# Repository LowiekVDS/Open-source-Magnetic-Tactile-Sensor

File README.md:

### TL;DR

[Paper](https://arxiv.org/abs/2405.18582), also see [this repo](https://github.com/LowiekVDS/masters-thesis) for expanded design.

# Open-source Magnetic Tactile Sensing

This repo contains the design files for a magnetic tactile fingertip presented at the [ViTac workshop](https://shanluo.github.io/ViTacWorkshops/) at ICRA2024, you can read the paper [here](https://arxiv.org/abs/2405.18582).
The fingertip has four taxels in a 2-by-2 grid. We developed a calibration method to be used with a robotic arm with integrated F/T sensor. In the paper, the fingertip is mounted to (a gripper the arm and pushed against an external probe to collect calibration data. It is crucial that the mounting of the fingertip to the robot is rigid. We have noticed that this is not sufficiently the case when mounting the fingertip to a Robotiq 2F-85 gripper. A Schunk EGK-40 gave better results. 

This work was expanded upon by designing a 4-by-8 grid as well, together with a more reliable calibration method where the sensor is mounted to the table, see [this repo](https://github.com/LowiekVDS/masters-thesis).

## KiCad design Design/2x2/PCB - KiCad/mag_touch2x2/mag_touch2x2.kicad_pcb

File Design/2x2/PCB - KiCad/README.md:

The KiCad component schematics and footprints are in the `lib` folder, make sure to add them in KiCad (Preferences > Manage Symbol Libraries && Preferences > Manage Footprint Libraries).

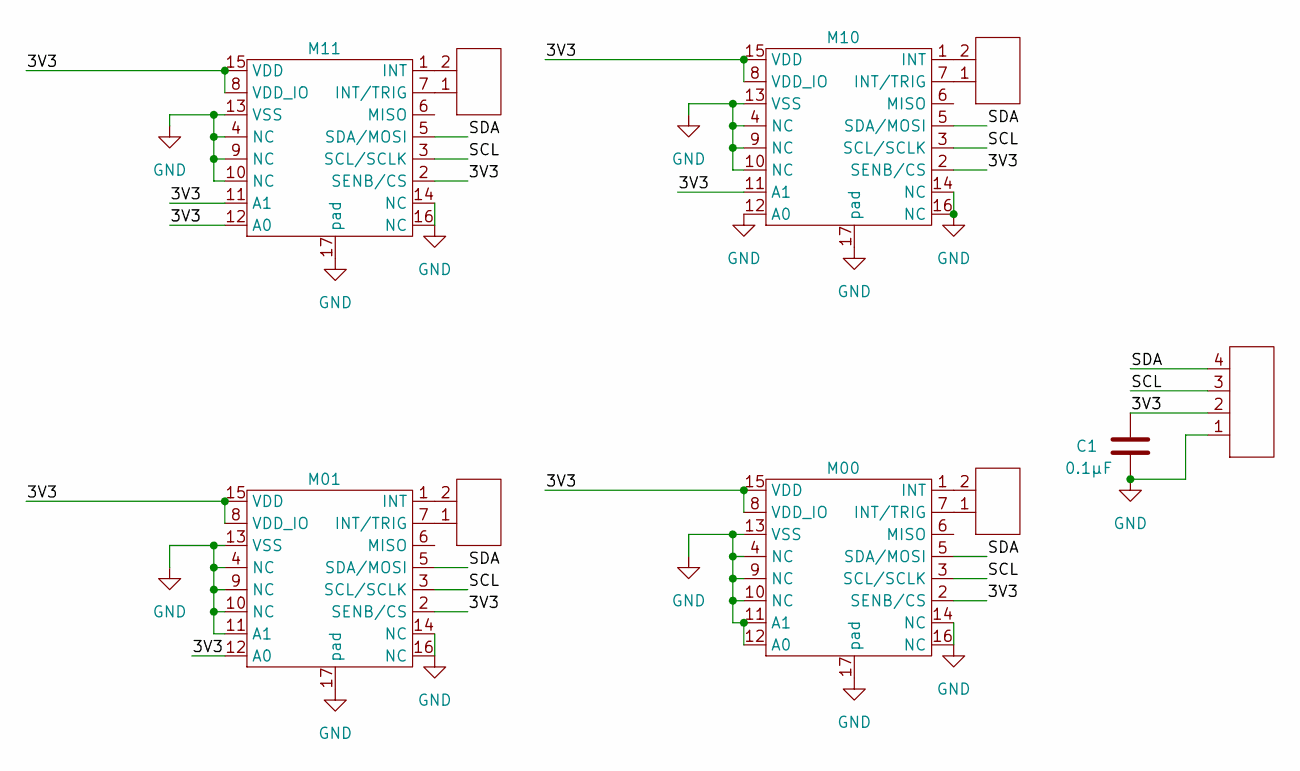
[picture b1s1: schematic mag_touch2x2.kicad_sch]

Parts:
C1: 0.1µF; C_0603_1608Metric
I1: 2POS_INTERFACE; 4POS_INTERFACE
I2, I3, I4, I5: 2POS_INTERFACE
M00, M01, M10, M11: QFN50P300X300X100-17N

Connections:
/3V3: C1.1, I1.2, M00.2 (SENB/CS), M00.8 (VDD_IO), M00.15 (VDD), M01.2 (SENB/CS), M01.8 (VDD_IO), M01.12 (A0), M01.15 (VDD), M10.2 (SENB/CS), M10.8 (VDD_IO), M10.11 (A1), M10.15 (VDD), M11.2 (SENB/CS), M11.8 (VDD_IO), M11.11 (A1), M11.12 (A0), M11.15 (VDD)
/SCL: I1.3, M00.3 (SCL/SCLK), M01.3 (SCL/SCLK), M10.3 (SCL/SCLK), M11.3 (SCL/SCLK)
/SDA: I1.4, M00.5 (SDA/MOSI), M01.5 (SDA/MOSI), M10.5 (SDA/MOSI), M11.5 (SDA/MOSI)
GND: C1.2, I1.1, M00.4 (NC), M00.9 (NC), M00.10 (NC), M00.11 (A1), M00.12 (A0), M00.13 (VSS), M00.14 (NC), M00.16 (NC), M00.17 (pad), M01.4 (NC), M01.9 (NC), M01.10 (NC), M01.11 (A1), M01.13 (VSS), M01.14 (NC), M01.16 (NC), M01.17 (pad), M10.4 (NC), M10.9 (NC), M10.10 (NC), M10.12 (A0), M10.13 (VSS), M10.14 (NC), M10.16 (NC), M10.17 (pad), M11.4 (NC), M11.9 (NC), M11.10 (NC), M11.13 (VSS), M11.14 (NC), M11.16 (NC), M11.17 (pad)
unnamed: I5.2, M00.1 (INT)
unnamed: I5.1, M00.7 (INT/TRIG)
unnamed: I4.2, M01.1 (INT)
unnamed: I4.1, M01.7 (INT/TRIG)
unnamed: I2.2, M10.1 (INT)
unnamed: I2.1, M10.7 (INT/TRIG)
unnamed: I3.2, M11.1 (INT)
unnamed: I3.1, M11.7 (INT/TRIG)

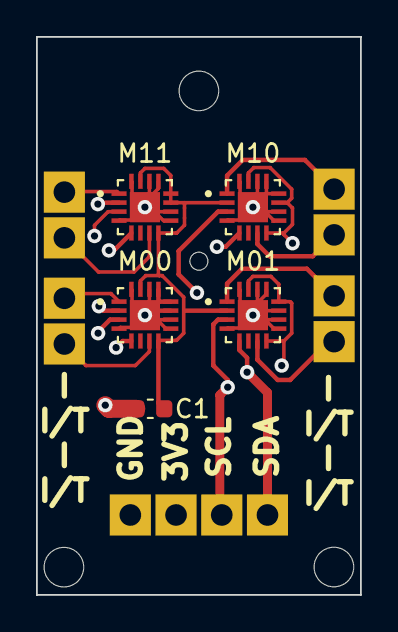
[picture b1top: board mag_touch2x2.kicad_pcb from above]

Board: 4 copper layers, 18.0 x 31.0 mm, 10 parts (0 on the bottom side), 12 nets.

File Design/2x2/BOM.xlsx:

Electrical (PCB)
Designator | Part | Example link
M00, M01, M10, M11 | MLX90393SLW-ABA-011-RE | https://www.digikey.be/nl/products/detail/melexis-technologi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
C1 | 100nF 0603 capacitor | https://www.digikey.be/nl/products/detail/kyocera-avx/06035C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
Mechanical
Item | Part | Example link
Silicone | Siliconen Additie Kleurloos 50 (hard) | https://www.siliconesandmore.com/nl/siliconen-additie-kleurl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
Silicone (soft alternative) | Siliconen Additie Kleurloos 5 | https://www.siliconesandmore.com/nl/siliconen-additie-kleurl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
Magnets ø1.5mm | DZ-001.5-001-G52 | https://www.neomagnete.de/en/disc-magnet-1-5x1mm-neodym-n52-gilded
Aluminium 1515 profile |  | https://www.123-3d.nl/123-3D-Aluminium-profiel-1515-lengte-1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
3D printed parts |  | https://jlc3dp.com/3d-printing-quote

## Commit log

2024-06-14 large update
2024-06-17 img update
2024-06-17 added cad files
